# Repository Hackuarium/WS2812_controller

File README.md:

# WS2812_Arduino
Small board compatible with Arduino to control WS2812

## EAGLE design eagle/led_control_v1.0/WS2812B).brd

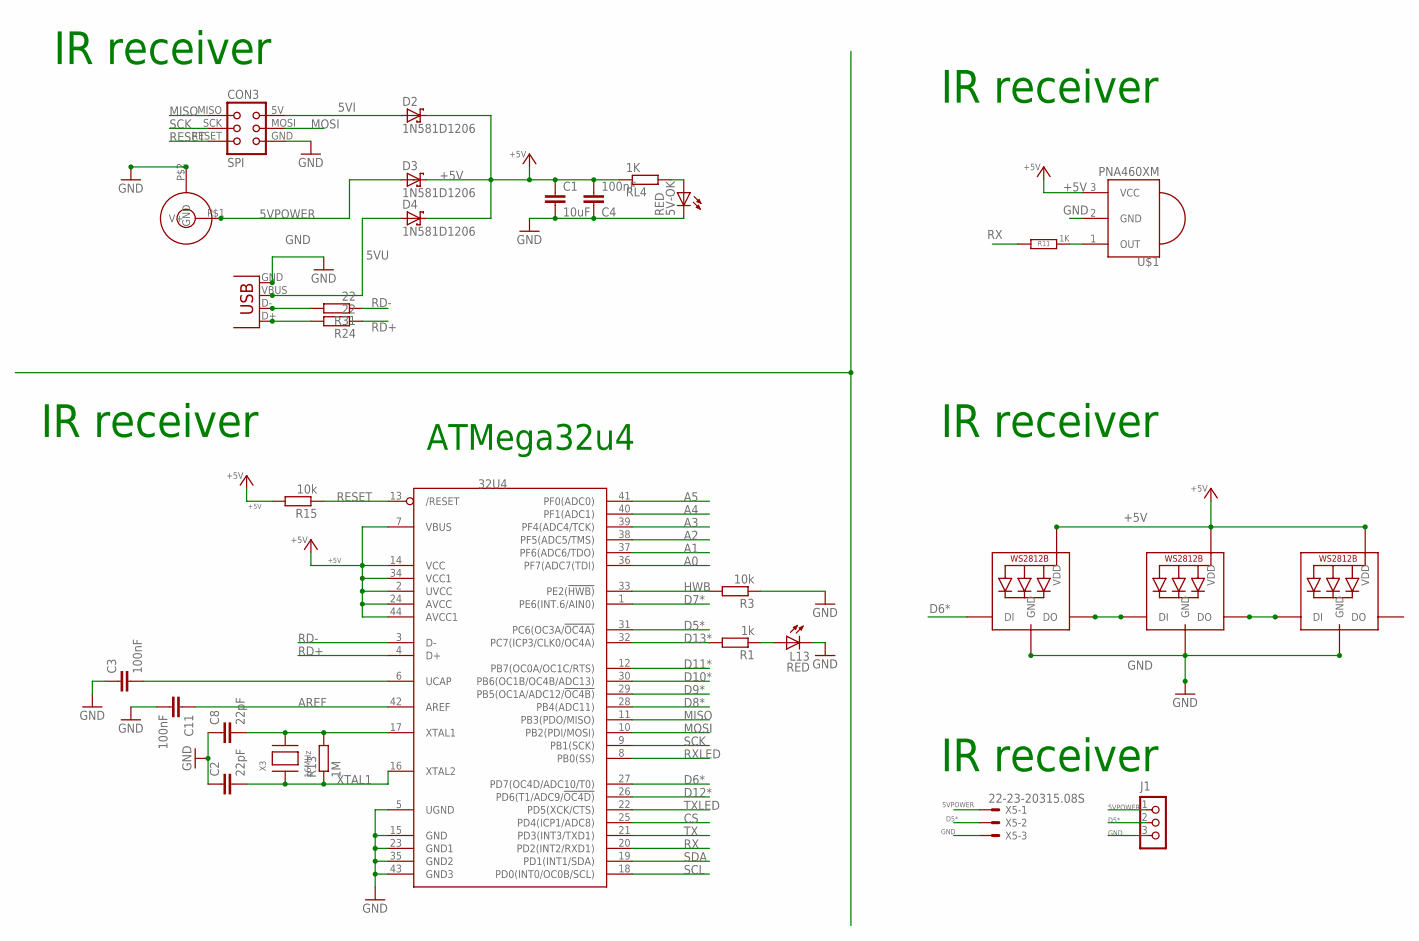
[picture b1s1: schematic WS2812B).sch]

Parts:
5V-OK: RED; CHIP-LED0805
C1: 10uF; C1206
C2, C8: 22pF; C0805K
C3, C11: 100nF; C0805K
C4: 100nF; C1206
CON2: JACK_DC_BARREL; DC_BARREL
CON3: SPI; TC2030-MCP-NL
D2, D3, D4: 1N581D1206; LED-1206
J1: CON_TERMINAL_BLOCK_03-5MM; TERMINAL_BLOCK_3P_5
L13: RED; CHIP-LED0805
LED1, LED2, LED3: WS2812B_5050N; WS2812B-NARROW
R1: 1k; M0805
R3, R15: 10k; M0805
R11: 1K; R0805
R13: 1M; M0805
R24, R31: 22; M0805
RL4: 1K; R0805
U$1: PNA460XM
U$4: 32U4; TQFP44
X2: USB-MICROB
X3: 16MHz; NX6035
X5: 22-23-20315.08S; 3-PIN-5.08S

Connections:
5VI: CON3.5V (VCC), D2.A
5VPOWER: CON2.P$1 (V+), D3.A, J1.1, X5.1
5VU: D4.A, X2.VBUS
+5V: C1.1, C4.2, D2.C, D3.C, D4.C, LED1.1-VDD (VDD), LED2.1-VDD (VDD), LED3.1-VDD (VDD), R15.2, RL4.1, U$1.3 (VCC), U$4.2 (UVCC), U$4.7 (VBUS), U$4.14 (VCC), U$4.24 (AVCC), U$4.34 (VCC1), U$4.44 (AVCC1)
A0: U$4.36 (PF7(ADC7(TDI))
A1: U$4.37 (PF6(ADC6/TDO))
A2: U$4.38 (PF5(ADC5/TMS))
A3: U$4.39 (PF4(ADC4/TCK))
A4: U$4.40 (PF1(ADC1))
A5: U$4.41 (PF0(ADC0))
AREF: C11.1, U$4.42 (AREF)
CS: U$4.25 (PD4(ICP1/ADC8))
D5*: J1.2, U$4.31 (PC6(OC3A/!OC4A)), X5.2
D6*: LED1.4-DIN (DI), U$4.27 (PD7(OC4D/ADC10/T0))
D7*: U$4.1 (PE6(INT.6/AIN0))
D8*: U$4.28 (PB4(ADC11))
D9*: U$4.29 (PB5(OC1A/ADC12/!OC4B))
D10*: U$4.30 (PB6(OC1B/OC4B/ADC13))
D11*: U$4.12 (PB7(OC0A/OC1C/RTS))
D12*: U$4.26 (PD6(T1/ADC9/!OC4D))
D13*: R1.2, U$4.32 (PC7(ICP3/CLK0/OC4A))
D_USB+: R24.2, X2.D+
D_USB-: R31.2, X2.D-
GND: 5V-OK.C, C1.2, C2.1, C3.1, C4.1, C8.1, C11.2, CON2.P$2 (GND), CON3.GND, J1.3, L13.C, LED1.3-GND (GND), LED2.3-GND (GND), LED3.3-GND (GND), R3.1, U$1.2 (GND), U$4.5 (UGND), U$4.15 (GND), U$4.23 (GND1), U$4.35 (GND2), U$4.43 (GND3), X2.GND, X5.3
HWB: R3.2, U$4.33 (PE2(!HWB))
MISO: CON3.MISO, U$4.11 (PB3(PDO/MISO))
MOSI: CON3.MOSI, U$4.10 (PB2(PDI/MOSI))
unnamed: LED1.2-DOUT (DO), LED2.4-DIN (DI)
unnamed: LED2.2-DOUT (DO), LED3.4-DIN (DI)
unnamed: L13.A, R1.1
unnamed: R11.1, U$1.1 (OUT)
unnamed: 5V-OK.A, RL4.2
unnamed: C3.2, U$4.6 (UCAP)
unnamed: C8.2, R13.2, U$4.17 (XTAL1), X3.P$2
RD+: R24.1, U$4.4 (D+)
RD-: R31.1, U$4.3 (D-)
RESET: CON3.RESET, R15.1, U$4.13 (/RESET)
RX: R11.2, U$4.20 (PD2(INT2/RXD1))
RXLED: U$4.8 (PB0(SS))
SCK: CON3.SCK, U$4.9 (PB1(SCK))
SCL: U$4.18 (PD0(INT0/OC0B/SCL))
SDA: U$4.19 (PD1(INT1/SDA))
TX: U$4.21 (PD3(INT3/TXD1))
TXLED: U$4.22 (PD5(XCK/CTS))
XTAL1: C2.2, R13.1, U$4.16 (XTAL2), X3.P$1

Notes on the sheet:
ATMega32u4
IR receiver

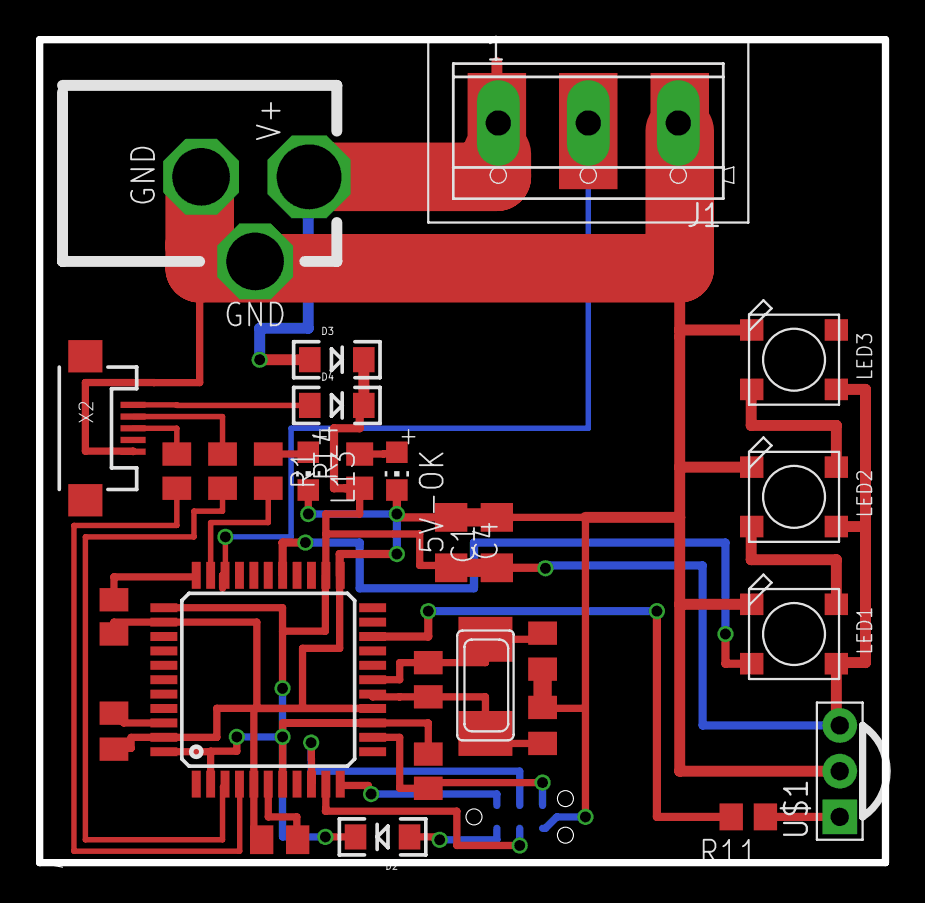
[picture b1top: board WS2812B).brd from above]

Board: 2 copper layers, 47.0 x 45.8 mm, 30 parts (1 on the bottom side), 27 nets.

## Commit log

2016-05-05 Add IR WS2812 code
2016-05-21 Correct pin
2017-12-26 add controller for nano
2018-10-14 start to add remote control with 44 buttons
2018-10-15 finish 44 buttons remote control
2018-10-21 improve code
2019-12-27 working on compatibility with 2 remotes
2020-03-23 feat: improve functions
2020-03-23 feat: add more color modes
2020-03-23 fix: simple remote control
2020-11-22 feat: Christmas tree
2020-11-24 feat: add firework
2020-11-25 feat: add tree
2020-11-29 feat: allow to change intensity and fix bugs
2020-12-11 feat: parameter to change color speed
2020-12-12 feat: many new parameters and optimization

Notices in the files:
parts and their libraries:
lpatiny: ©2009 ROFA.cz - modified and updated by Robert Darlington ‹rdarlington@gmail.com›
SparkFun: Licensing: CC v3.0 Share-Alike You are welcome to use this library for commercial purposes.
